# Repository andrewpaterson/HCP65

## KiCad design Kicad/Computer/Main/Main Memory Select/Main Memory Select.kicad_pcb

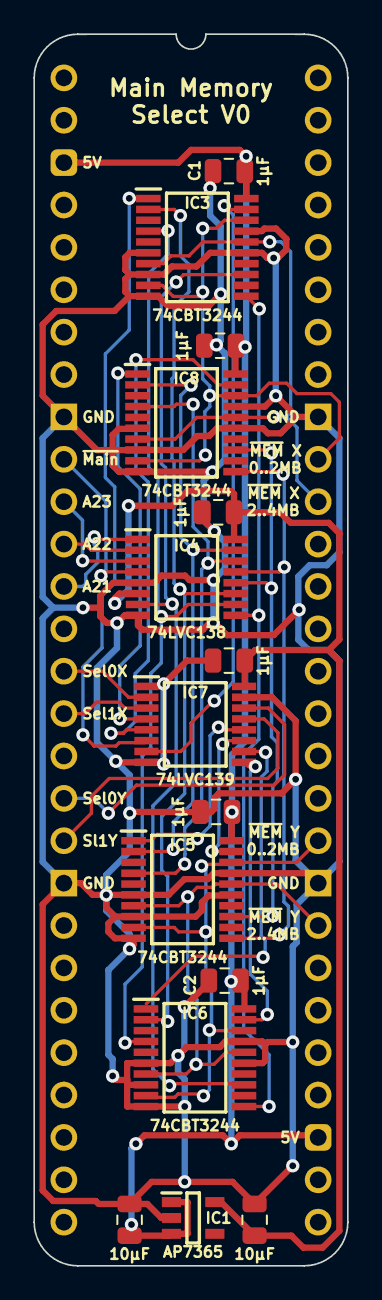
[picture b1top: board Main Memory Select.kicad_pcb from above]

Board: 2 copper layers, 18.8 x 73.8 mm, 16 parts (0 on the bottom side), 31 nets.

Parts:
C1, C2, C3, C5, C9, C12: 1μF; C_0805
C10, C11: 10µF; C_0805
IC1: AP7365-33WG-7; SOT95P285X130-5N
IC3, IC5, IC6, IC8: SN74CBT3244CPWR; SOP65P640X120-20N
IC4: 74LVC138APW-Q100J; SOP65P640X110-16N
IC7: 74LVC139PW,118; SOP65P640X110-16N
J1: Board 2x28 W15.24mm; DIP-56_Board_W15.24mm

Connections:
5V: C1.1, C2.1, C3.1, C9.1, C10.1, IC1.1 (6VIn), IC1.3 (EN), IC3.20 (5V), IC5.20 (5V), IC6.20 (5V), IC8.20 (5V), J1.3, J1.31
/3.3V: C5.1, C11.1, C12.1, IC1.5 (3.3VOut), IC4.6 (E3), IC4.16 (3V), IC7.16 (3V)
/Memory 0..2MB ~CS: IC4.15 (~Y0), IC5.2 (1A1), IC8.2 (1A1)
/Memory 0..4MB_{ Device}X: IC7.4 (~1Y0), IC8.1 (1~OE)
/Memory 0..4MB_{ Device}Y: IC5.1 (1~OE), IC7.12 (~2Y0)
/Memory 2..4MB ~CS: IC4.14 (~Y1), IC5.4 (1A2), IC8.4 (1A2)
/Memory 4..6MB ~CS: IC4.13 (~Y2), IC5.11 (2A1), IC8.11 (2A1)
/Memory 4..8MB_{ Device}X: IC7.5 (~1Y1), IC8.19 (2~OE)
/Memory 4..8MB_{ Device}Y: IC5.19 (2~OE), IC7.11 (~2Y1)
/Memory 6..8MB ~CS: IC4.12 (~Y3), IC5.13 (2A2), IC8.13 (2A2)
/Memory 8..10MB ~CS: IC3.2 (1A1), IC4.11 (~Y4), IC6.2 (1A1)
/Memory 8..12MB_{ Device}X: IC3.1 (1~OE), IC7.6 (~1Y2)
/Memory 8..12MB_{ Device}Y: IC6.1 (1~OE), IC7.10 (~2Y2)
/Memory 10..12MB ~CS: IC3.4 (1A2), IC4.10 (~Y5), IC6.4 (1A2)
/Memory 12..14MB ~CS: IC3.11 (2A1), IC4.9 (~Y6), IC6.11 (2A1)
/Memory 12..16MB_{ Device}X: IC3.19 (2~OE), IC7.7 (~1Y3)
/Memory 12..16MB_{ Device}Y: IC6.19 (2~OE), IC7.9 (~2Y3)
/Memory 14..16MB ~CS: IC3.13 (2A2), IC4.7 (~Y7), IC6.13 (2A2)
AM21: IC4.1 (A0), J1.13
AM22: IC4.2 (A1), J1.12
AM23: IC4.3 (A2), J1.11
GND: C1.2, C2.2, C3.2, C5.2, C9.2, C10.2, C11.2, C12.2, IC1.2 (GND), IC3.6 (1A3), IC3.8 (1A4), IC3.10 (GND), IC3.15 (2A3), IC3.17 (2A4), IC4.5 (~E2), IC4.8 (GND), IC5.6 (1A3), IC5.8 (1A4), IC5.10 (GND), IC5.15 (2A3), IC5.17 (2A4), IC6.6 (1A3), IC6.8 (1A4), IC6.10 (GND), IC6.15 (2A3), IC6.17 (2A4), IC7.1 (~1E), IC7.8 (GND), IC7.15 (~2E), IC8.6 (1A3), IC8.8 (1A4), IC8.10 (GND), IC8.15 (2A3), IC8.17 (2A4), J1.9, J1.20, J1.37, J1.48
Select 0_{ Device}X: IC7.2 (1A0), J1.15
Select 0_{ Device}Y: IC7.14 (2A0), J1.18
Select 1_{ Device}X: IC7.3 (1A1), J1.16
Select 1_{ Device}Y: IC7.13 (2A1), J1.19
~Main_{M}: IC4.4 (~E1), J1.10
~Memory _{0..2MB}_{ Device}X: IC3.9 (2B1), IC3.18 (1B1), IC8.9 (2B1), IC8.18 (1B1), J1.47
~Memory _{0..2MB}_{ Device}Y: IC5.9 (2B1), IC5.18 (1B1), IC6.9 (2B1), IC6.18 (1B1), J1.38
~Memory _{2..4MB}_{ Device}X: IC3.7 (2B2), IC3.16 (1B2), IC8.7 (2B2), IC8.16 (1B2), J1.46
~Memory _{2..4MB}_{ Device}Y: IC5.7 (2B2), IC5.16 (1B2), IC6.7 (2B2), IC6.16 (1B2), J1.36

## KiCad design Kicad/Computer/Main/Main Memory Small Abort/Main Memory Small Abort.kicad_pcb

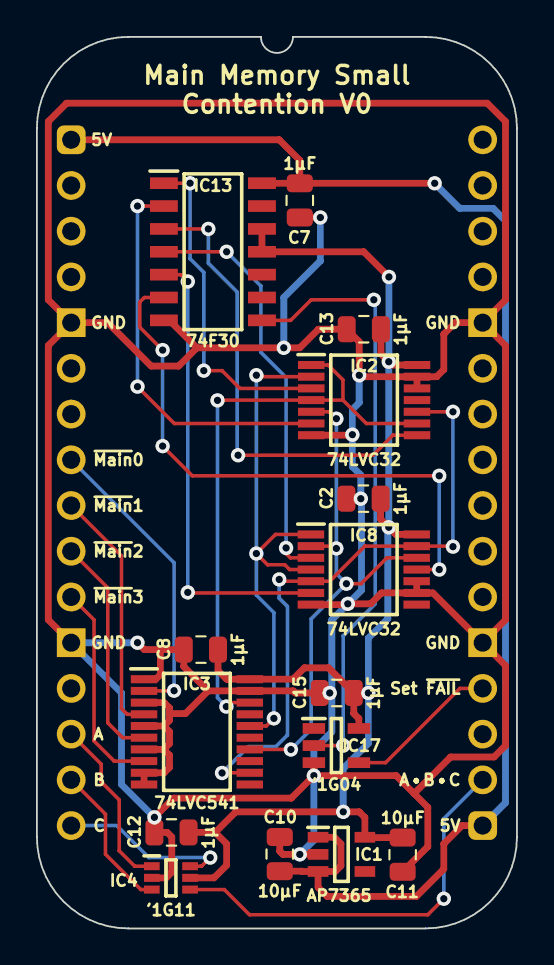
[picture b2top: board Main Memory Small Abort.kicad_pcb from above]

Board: 2 copper layers, 26.7 x 49.5 mm, 16 parts (0 on the bottom side), 23 nets.

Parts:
C2, C7, C8, C12, C13, C15: 1μF; C_0805
C10, C11: 10µF; C_0805
IC1: AP7365-33WG-7; SOT95P285X130-5N
IC2, IC8: 74LVC32APW,118; SOP65P640X110-14N
IC3: 74LVC541APW,118; SOP65P640X110-20N
IC4: 74LVC1G11GW-Q100H; SOP65P210X110-6N
IC13: SN74F30DR; SOIC127P600X175-14N
IC17: 74LVC1G04GV,125; SOT95P275X110-5N
J1: Board 2x16 W22.86mm; DIP-32_Board_W22.86mm

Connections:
5V: C7.1, C10.1, IC1.1 (6VIn), IC1.3 (EN), IC13.14 (5V), J1.1, J1.17
/3.3V: C2.1, C8.1, C11.1, C12.1, C13.1, C15.1, IC1.5 (3.3VOut), IC2.14 (3V), IC3.20 (3V), IC4.5 (3V), IC8.14 (3V), IC13.11 (G), IC13.12 (H), IC17.5 (3V)
/~0+1: IC2.3 (1Y), IC13.1 (A)
/~0+2: IC2.6 (2Y), IC13.2 (B)
/~0+3: IC2.8 (3Y), IC13.3 (C)
/~1+2: IC8.3 (1Y), IC13.4 (D)
/~1+3: IC8.6 (2Y), IC13.5 (E)
/~2+3: IC8.11 (4Y), IC13.6 (F)
/~MainB0: IC2.1 (1A), IC2.4 (2A), IC2.9 (3A), IC3.18 (Y0)
/~MainB1: IC2.2 (1B), IC3.16 (Y2), IC8.1 (1A), IC8.4 (2A)
/~MainB2: IC2.5 (2B), IC3.14 (Y4), IC8.2 (1B), IC8.12 (4A)
/~MainB3: IC2.10 (3B), IC3.12 (Y6), IC8.5 (2B), IC8.13 (4B)
A: IC4.1 (A), J1.14
A•B•C: IC4.4 (Y), J1.18
B: IC4.3 (B), J1.15
C: IC4.6 (C), J1.16
GND: C2.2, C7.2, C8.2, C10.2, C11.2, C12.2, C13.2, C15.2, IC1.2 (GND), IC2.7 (GND), IC2.12 (4A), IC2.13 (4B), IC3.1 (~OE1), IC3.3 (A1), IC3.5 (A3), IC3.7 (A5), IC3.9 (A7), IC3.10 (GND), IC3.19 (~OE2), IC4.2 (GND), IC8.7 (GND), IC8.9 (3A), IC8.10 (3B), IC13.7 (GND), IC17.3 (GND), J1.5, J1.12, J1.21, J1.28
unnamed: IC13.8 (Y), IC17.2 (A)
~Main0: IC3.2 (A0), J1.8
~Main1: IC3.4 (A2), J1.9
~Main2: IC3.6 (A4), J1.10
~Main3: IC3.8 (A6), J1.11
~Set Contention: IC17.4 (Y), J1.20

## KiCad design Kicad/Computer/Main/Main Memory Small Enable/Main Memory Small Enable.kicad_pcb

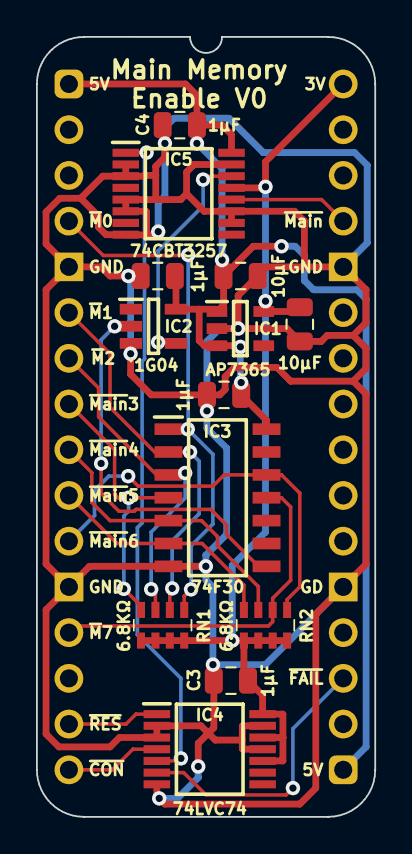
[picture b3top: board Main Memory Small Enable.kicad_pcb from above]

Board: 2 copper layers, 18.8 x 43.3 mm, 14 parts (0 on the bottom side), 18 nets.

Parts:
C1, C3, C4, C6: 1μF; C_0805
C10, C11: 10µF; C_0805
IC1: AP7365-33WG-7; SOT95P285X130-5N
IC2: 74LVC1G04GV,125; SOT95P275X110-5N
IC3: SN74F30DR; SOIC127P600X175-14N
IC4: 74LVC74APW,118; SOP65P640X110-14N
IC5: SN74CBT3257CPWR; SOP65P640X120-16N
J2: Board 2x16 W15.24mm; DIP-32_Board_W15.24mm
RN1, RN2: CAY16-682J4LF; CAY16-J4

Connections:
3.3V: C3.1, C11.1, IC1.5 (3.3VOut), IC4.10 (~2SD), IC4.12 (2D), IC4.14 (3V), IC5.13 (4B2), J2.32, RN1.5 (R4), RN1.6 (R3), RN1.7 (R2), RN1.8 (R1), RN2.5 (R4), RN2.6 (R3), RN2.7 (R2), RN2.8 (R1)
5V: C1.1, C4.1, C6.1, C10.1, IC1.1 (6VIn), IC1.3 (EN), IC2.5 (3V), IC3.14 (5V), IC5.16 (5V), J2.1, J2.17
/Contention: IC4.5 (1Q), IC5.1 (S)
/Pre-Main Memory: IC2.2 (A), IC3.8 (Y)
/~Pre-Main Memory: IC2.4 (Y), IC5.14 (4B1)
GND: C1.2, C3.2, C4.2, C6.2, C10.2, C11.2, IC1.2 (GND), IC2.3 (GND), IC3.7 (GND), IC4.2 (1D), IC4.3 (1CP), IC4.7 (GND), IC4.11 (2CP), IC4.13 (~2RD), IC5.2 (1B1), IC5.3 (1B2), IC5.5 (2B1), IC5.6 (2B2), IC5.8 (GND), IC5.10 (3B2), IC5.11 (3B1), IC5.15 (~OE), J2.5, J2.12, J2.21, J2.28
~Contention: IC4.6 (~1Q), J2.19
~Main Memory: IC5.12 (4A), J2.29
~Main0: IC3.1 (A), J2.4, RN1.1 (R1)
~Main1: IC3.2 (B), J2.6, RN1.2 (R2)
~Main2: IC3.3 (C), J2.7, RN1.3 (R3)
~Main3: IC3.4 (D), J2.8, RN1.4 (R4)
~Main4: IC3.5 (E), J2.9, RN2.3 (R3)
~Main5: IC3.6 (F), J2.10, RN2.4 (R4)
~Main6: IC3.12 (H), J2.11, RN2.1 (R1)
~Main7: IC3.11 (G), J2.13, RN2.2 (R2)
~Reset: IC4.1 (~1RD), J2.15
~Set Contention: IC4.4 (~1SD), J2.16

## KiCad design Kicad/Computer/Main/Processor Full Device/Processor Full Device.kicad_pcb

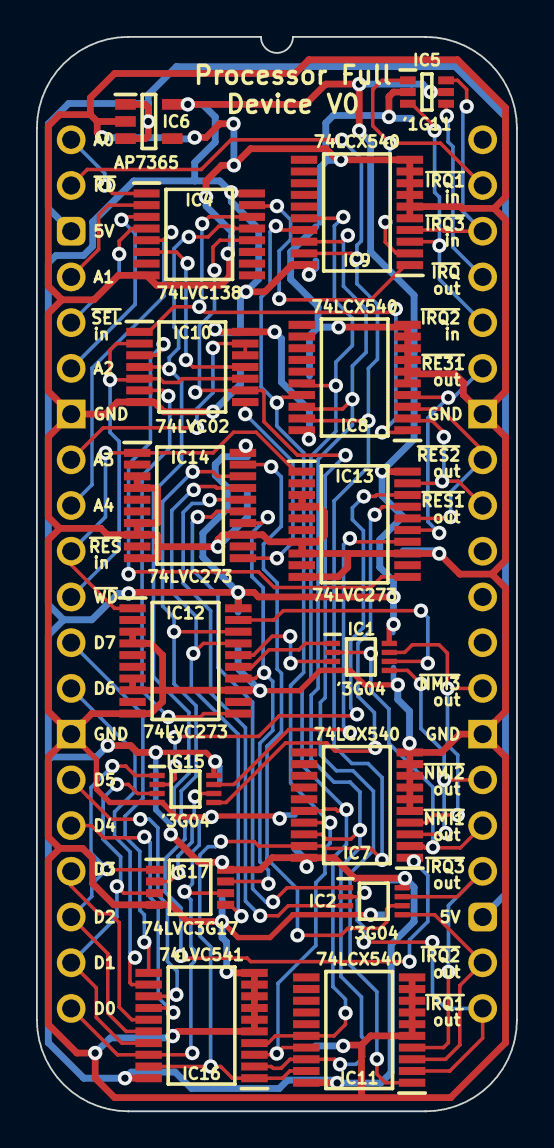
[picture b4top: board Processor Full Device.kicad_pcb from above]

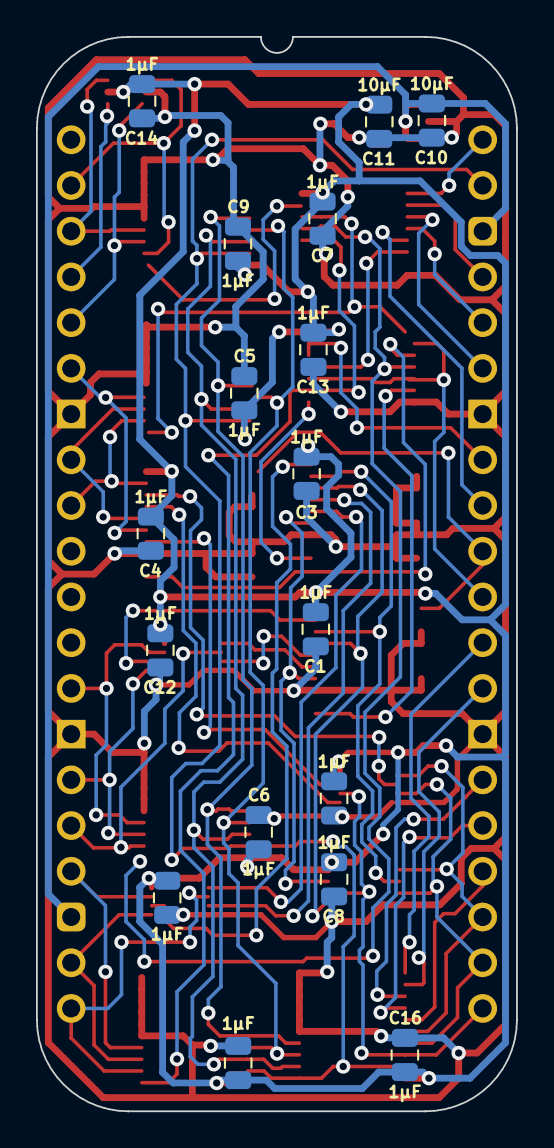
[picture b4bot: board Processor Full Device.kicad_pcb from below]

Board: 2 copper layers, 26.7 x 59.7 mm, 34 parts (17 on the bottom side), 56 nets.

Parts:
C1, C2, C3, C4, C5, C6, C7, C8, C9, C12, C13, C14, C15, C16, C17: 1μF; C_0805
C10, C11: 10µF; C_0805
IC1, IC2, IC15: SN74LVC3G04DCUR; SOP50P310X90-8N
IC4: 74LVC138APW-Q100J; SOP65P640X110-16N
IC5: 74LVC1G11GW-Q100H; SOP65P210X110-6N
IC6: AP7365-33WG-7; SOT95P285X130-5N
IC7, IC8, IC9, IC11: 74LCX540FT; SOP65P640X120-20N
IC10: 74LVC02APW,118; SOP65P640X110-14N
IC12, IC13, IC14: 74LVC273PW,118; SOP65P640X110-20N
IC16: 74LVC541APW,118; SOP65P640X110-20N
IC17: 74LVC3G17DP,125; SOP65P400X110-8N
J1: Board 2x20 W22.86mm; DIP-40_Board_W22.86mm

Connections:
5V: C10.1, IC6.1 (6VIn), IC6.3 (EN), J1.3, J1.23
/3.3V: C1.1, C2.1, C3.1, C4.1, C5.1, C6.1, C7.1, C8.1, C9.1, C11.1, C12.1, C13.1, C14.1, C15.1, C16.1, C17.1, IC1.8 (3V), IC2.8 (3V), IC4.16 (3V), IC5.5 (3V), IC6.5 (3.3VOut), IC7.20 (3V), IC8.20 (3V), IC9.20 (3V), IC10.14 (3V), IC11.20 (3V), IC12.20 (3V), IC13.20 (3V), IC14.20 (3V), IC15.8 (3V), IC16.20 (3V), IC17.8 (3V)
/DI0: IC12.18 (D7), IC14.18 (D7), IC17.2 (3Y)
/DI1: IC12.17 (D6), IC14.17 (D6), IC17.5 (2Y)
/DI2: IC12.14 (D5), IC14.14 (D5), IC17.7 (1Y)
/DO0: IC7.18 (~Y1), IC8.18 (~Y1), IC9.18 (~Y1), IC11.18 (~Y1), IC16.2 (A0)
/DO1: IC7.17 (~Y2), IC8.17 (~Y2), IC9.17 (~Y2), IC11.17 (~Y2), IC16.3 (A1)
/DO2: IC7.16 (~Y3), IC8.16 (~Y3), IC9.16 (~Y3), IC11.16 (~Y3), IC16.4 (A2)
/MPU1 IRQ_{out}: IC2.6 (3A), IC14.19 (Q7)
/MPU1 NMI_{out}: IC1.6 (3A), IC12.19 (Q7)
/MPU2 IRQ_{out}: IC2.3 (2A), IC14.16 (Q6)
/MPU2 NMI_{out}: IC1.3 (2A), IC12.16 (Q6)
/MPU3 IRQ_{out}: IC2.1 (1A), IC14.15 (Q5)
/MPU3 NMI_{out}: IC1.1 (1A), IC12.15 (Q5)
/Y1•WD: IC10.3 (1Y), IC13.11 (CP)
/Y2•WD: IC10.6 (2Y), IC12.11 (CP)
/Y3•WD: IC10.8 (3Y), IC14.11 (CP)
/~A3: IC4.6 (E3), IC10.11 (4Y)
/~D0: IC13.18 (D7), IC15.2 (3Y)
/~D1: IC13.17 (D6), IC15.5 (2Y)
/~D2: IC13.14 (D5), IC15.7 (1Y)
/~Y0: IC4.15 (~Y0), IC9.1 (~OE1)
/~Y1: IC4.14 (~Y1), IC8.1 (~OE1), IC10.1 (1A)
/~Y2: IC4.13 (~Y2), IC7.1 (~OE1), IC10.4 (2A)
/~Y3: IC4.12 (~Y3), IC10.9 (3A), IC11.1 (~OE1)
A0: IC4.1 (A0), J1.1
A1: IC4.2 (A1), J1.4
A2: IC4.3 (A2), J1.6
A3: IC10.12 (4A), IC10.13 (4B), J1.8
A4: IC4.5 (~E2), J1.9
D0: IC15.6 (3A), IC16.18 (Y0), IC17.6 (3A), J1.20
D1: IC15.3 (2A), IC16.17 (Y1), IC17.3 (2A), J1.19
D2: IC15.1 (1A), IC16.16 (Y2), IC17.1 (1A), J1.18
D3: IC16.15 (Y3), J1.17
D4: IC16.14 (Y4), J1.16
D5: IC16.13 (Y5), J1.15
D6: IC16.12 (Y6), J1.13
D7: IC16.11 (Y7), J1.12
GND: C1.2, C2.2, C3.2, C4.2, C5.2, C6.2, C7.2, C8.2, C9.2, C10.2, C11.2, C12.2, C13.2, C14.2, C15.2, C16.2, C17.2, IC1.4 (GND), IC2.4 (GND), IC4.8 (GND), IC5.2 (GND), IC6.2 (GND), IC7.5 (A4), IC7.6 (A5), IC7.7 (A6), IC7.8 (A7), IC7.9 (A8), IC7.10 (GND), IC8.5 (A4), IC8.6 (A5), IC8.7 (A6), IC8.8 (A7), IC8.9 (A8), IC8.10 (GND), IC9.5 (A4), IC9.6 (A5), IC9.7 (A6), IC9.8 (A7), IC9.9 (A8), IC9.10 (GND), IC10.7 (GND), IC11.5 (A4), IC11.6 (A5), IC11.7 (A6), IC11.8 (A7), IC11.9 (A8), IC11.10 (GND), IC12.3 (D0), IC12.4 (D1), IC12.7 (D2), IC12.8 (D3), IC12.10 (GND), IC12.13 (D4), IC13.3 (D0), IC13.4 (D1), IC13.7 (D2), IC13.8 (D3), IC13.10 (GND), IC13.13 (D4), IC14.3 (D0), IC14.4 (D1), IC14.7 (D2), IC14.8 (D3), IC14.10 (GND), IC14.13 (D4), IC15.4 (GND), IC16.5 (A3), IC16.6 (A4), IC16.7 (A5), IC16.8 (A6), IC16.9 (A7), IC16.10 (GND), IC17.4 (GND), J1.7, J1.14, J1.27, J1.34
~Device Interrupt: IC5.4 (Y), J1.37
~Device Reset: IC12.1 (~MR), IC13.1 (~MR), IC14.1 (~MR), J1.10
~Device Select: IC4.4 (~E1), J1.5
~MPU1 IRQ_{in}: IC5.1 (A), IC9.2 (A1), J1.39
~MPU1 IRQ_{out}: IC2.2 (3Y), IC11.2 (A1), J1.21
~MPU1 NMI_{out}: IC1.2 (3Y), IC7.2 (A1), J1.25
~MPU1 Reset_{out}: IC8.2 (A1), IC13.19 (Q7), J1.32
~MPU2 IRQ_{in}: IC5.3 (B), IC9.3 (A2), J1.36
~MPU2 IRQ_{out}: IC2.5 (2Y), IC11.3 (A2), J1.22
~MPU2 NMI_{out}: IC1.5 (2Y), IC7.3 (A2), J1.26
~MPU2 Reset_{out}: IC8.3 (A2), IC13.16 (Q6), J1.33
~MPU3 IRQ_{in}: IC5.6 (C), IC9.4 (A3), J1.38
~MPU3 IRQ_{out}: IC2.7 (1Y), IC11.4 (A3), J1.24
~MPU3 NMI_{out}: IC1.7 (1Y), IC7.4 (A3), J1.28
~MPU3 Reset_{out}: IC8.4 (A3), IC13.15 (Q5), J1.35
~RD: IC7.19 (~OE2), IC8.19 (~OE2), IC9.19 (~OE2), IC11.19 (~OE2), IC16.1 (~OE1), IC16.19 (~OE2), J1.2
~WD: IC10.2 (1B), IC10.5 (2B), IC10.10 (3B), J1.11

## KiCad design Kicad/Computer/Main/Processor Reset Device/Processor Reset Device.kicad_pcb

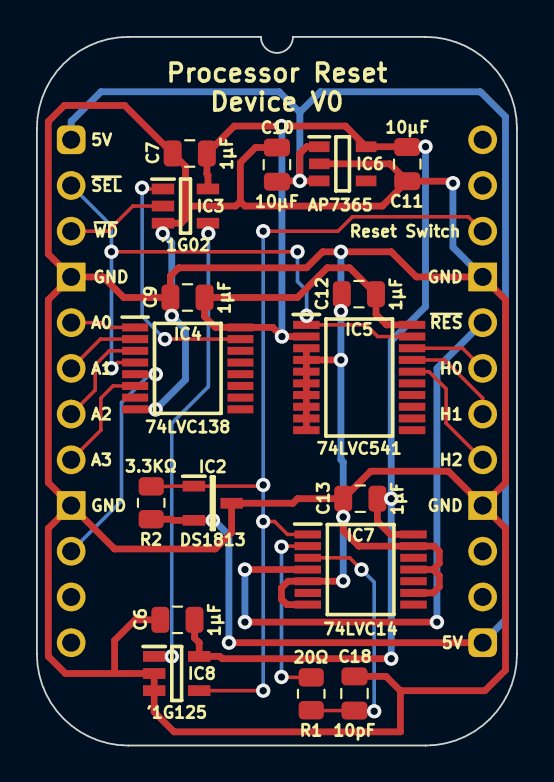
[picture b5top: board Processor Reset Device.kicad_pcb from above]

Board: 2 copper layers, 26.7 x 39.4 mm, 19 parts (1 on the bottom side), 19 nets.

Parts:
C6, C7, C9, C12, C13: 1μF; C_0805
C10, C11: 10µF; C_0805
C18: 10pF; C_0805
IC2: DS1813R-10+T&R; SOT95P237X112-3N
IC3: 74LVC1G02GV,125; SOT95P275X110-5N
IC4: 74LVC138APW-Q100J; SOP65P640X110-16N
IC5: 74LVC541APW,118; SOP65P640X110-20N
IC6: AP7365-33WG-7; SOT95P285X130-5N
IC7: 74LVC14APW,118; SOP65P640X110-14N
IC8: 74LVC1G125GV-Q100; SOT95P275X110-5N
J1: Board 2x12 W22.86mm; DIP-24_Board_W22.86mm
J4: Pin_Header_01x12; PinHeader_1x12_P2.54mm_Vertical
R1: 20Ω; R_0805
R2: 3.3KΩ; R_0805

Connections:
5V: C10.1, IC2.2 (5V), IC6.1 (6VIn), IC6.3 (EN), J1.1, J1.13, R2.2
/3.3V: C6.1, C7.1, C9.1, C11.1, C12.1, C13.1, IC3.5 (3V), IC4.16 (3V), IC5.2 (A0), IC5.20 (3V), IC6.5 (3.3VOut), IC7.14 (3V), IC8.5 (3V)
/Reset_{1}: IC7.2 (1Y), R1.1
/Reset_{2}: C18.1, IC7.3 (2A), R1.2
/~WD•~Y0: IC3.4 (Y), IC8.1 (~OE)
/~Y0: IC3.1 (B), IC4.15 (~Y0)
A0: IC4.1 (A0), J1.5
A1: IC4.2 (A1), J1.6
A2: IC4.3 (A2), J1.7
A3: IC4.6 (E3), J1.8
A4: IC4.5 (~E2), J1.10
GND: C6.2, C7.2, C9.2, C10.2, C11.2, C12.2, C13.2, C18.2, IC2.3 (GND), IC3.3 (GND), IC4.8 (GND), IC5.3 (A1), IC5.4 (A2), IC5.5 (A3), IC5.6 (A4), IC5.7 (A5), IC5.8 (A6), IC5.9 (A7), IC5.10 (GND), IC6.2 (GND), IC7.5 (3A), IC7.7 (GND), IC7.9 (4A), IC7.11 (5A), IC7.13 (6A), IC8.2 (A), IC8.3 (GND), J1.4, J1.9, J1.16, J1.21
H0: IC5.18 (Y0), J1.19
H1: IC5.17 (Y1), J1.18
H2: IC5.16 (Y2), J1.17
~Device Select: IC4.4 (~E1), IC5.1 (~OE1), IC5.19 (~OE2), J1.2
~Reset Switch: IC2.1 (~RST), IC7.1 (1A), IC8.4 (Y), J1.22, R2.1
~Reset: IC7.4 (2Y), J1.20
~WD: IC3.2 (A), J1.3

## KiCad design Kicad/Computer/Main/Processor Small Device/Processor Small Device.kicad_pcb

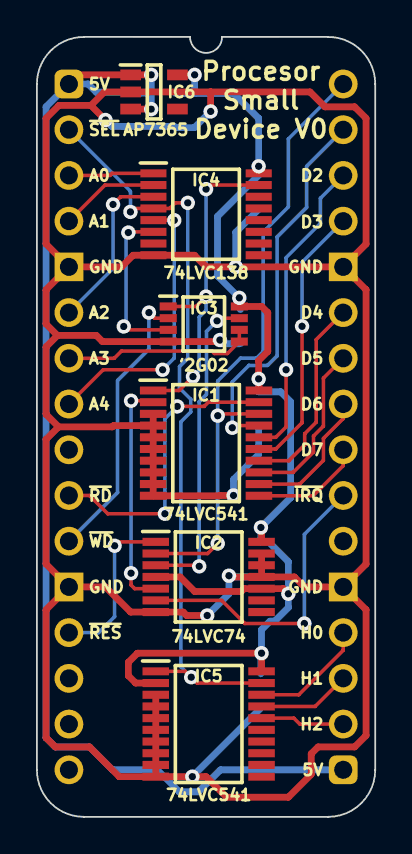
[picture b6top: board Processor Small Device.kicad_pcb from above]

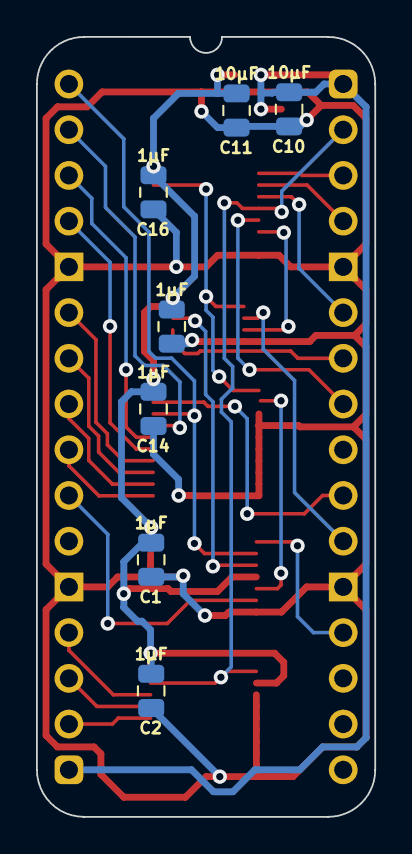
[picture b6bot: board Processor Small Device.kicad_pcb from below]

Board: 2 copper layers, 18.8 x 43.3 mm, 14 parts (7 on the bottom side), 28 nets.

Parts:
C1, C2, C14, C15, C16: 1μF; C_0805
C10, C11: 10µF; C_0805
IC1, IC5: 74LVC541APW,118; SOP65P640X110-20N
IC2: 74LVC74APW,118; SOP65P640X110-14N
IC3: 74LVC2G02DP,125; SOP65P400X110-8N
IC4: 74LVC138APW-Q100J; SOP65P640X110-16N
IC6: AP7365-33WG-7; SOT95P285X130-5N
J1: Board 2x16 W15.24mm; DIP-32_Board_W15.24mm

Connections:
5V: C10.1, IC6.1 (6VIn), IC6.3 (EN), J1.1, J1.17
/3.3V: C1.1, C2.1, C11.1, C14.1, C15.1, C16.1, IC1.20 (3V), IC2.4 (~1SD), IC2.10 (~2SD), IC2.14 (3V), IC3.8 (3V), IC4.16 (3V), IC5.2 (A0), IC5.20 (3V), IC6.5 (3.3VOut)
/MPU0 IRQ_{out}: IC1.2 (A0), IC2.5 (1Q)
/Y0•WD: IC2.3 (1CP), IC3.7 (1Y)
/~A3: IC3.3 (2Y), IC4.6 (E3)
/~Y0: IC1.1 (~OE1), IC3.1 (1A), IC4.15 (~Y0)
A0: IC4.1 (A0), J1.3
A1: IC4.2 (A1), J1.4
A2: IC4.3 (A2), J1.6
A3: IC3.5 (2A), IC3.6 (2B), J1.7
A4: IC4.5 (~E2), J1.8
D0: IC1.18 (Y0), IC2.2 (1D), J1.32
D1: IC1.17 (Y1), J1.31
D2: IC1.16 (Y2), J1.30
D3: IC1.15 (Y3), J1.29
D4: IC1.14 (Y4), J1.27
D5: IC1.13 (Y5), J1.26
D6: IC1.12 (Y6), J1.25
D7: IC1.11 (Y7), J1.24
GND: C1.2, C2.2, C10.2, C11.2, C14.2, C15.2, C16.2, IC1.3 (A1), IC1.4 (A2), IC1.5 (A3), IC1.6 (A4), IC1.7 (A5), IC1.8 (A6), IC1.9 (A7), IC1.10 (GND), IC2.7 (GND), IC2.11 (2CP), IC2.12 (2D), IC2.13 (~2RD), IC3.4 (GND), IC4.8 (GND), IC5.3 (A1), IC5.4 (A2), IC5.5 (A3), IC5.6 (A4), IC5.7 (A5), IC5.8 (A6), IC5.9 (A7), IC5.10 (GND), IC6.2 (GND), J1.5, J1.12, J1.21, J1.28
H0: IC5.18 (Y0), J1.20
H1: IC5.17 (Y1), J1.19
H2: IC5.16 (Y2), J1.18
~Device Reset: IC2.1 (~1RD), J1.13
~Device Select: IC4.4 (~E1), IC5.1 (~OE1), IC5.19 (~OE2), J1.2
~MPU0 IRQ_{out}: IC2.6 (~1Q), J1.23
~RD: IC1.19 (~OE2), J1.10
~WD: IC3.2 (1B), J1.11

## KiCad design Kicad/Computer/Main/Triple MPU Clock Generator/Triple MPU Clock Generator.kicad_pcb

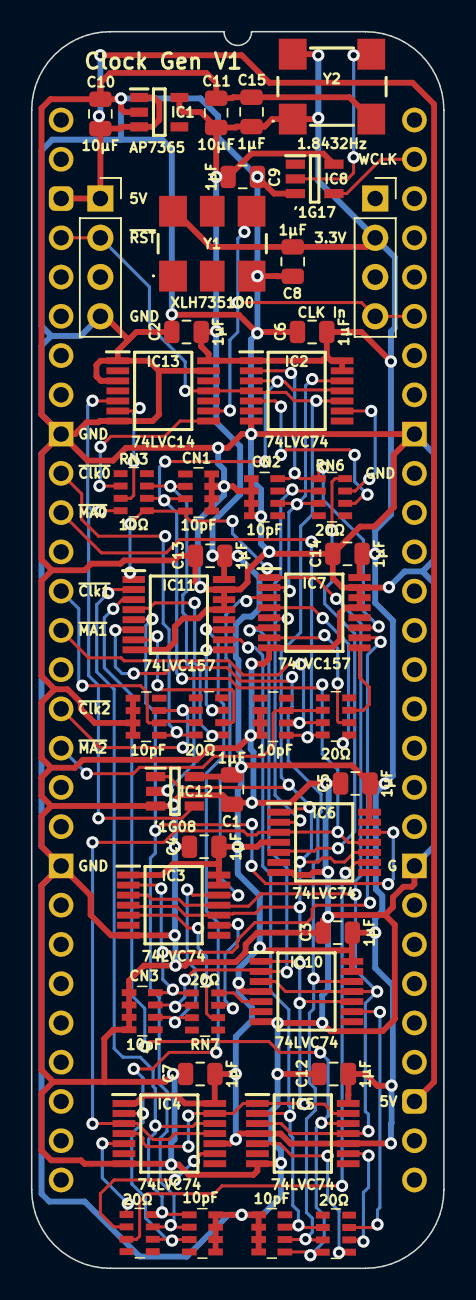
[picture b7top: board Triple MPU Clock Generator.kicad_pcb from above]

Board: 2 copper layers, 26.7 x 80.0 mm, 46 parts (0 on the bottom side), 49 nets.

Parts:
C1, C2, C3, C4, C5, C6, C7, C8, C9, C12, C13, C14, C15: 1μF; C_0805
C10, C11: 10µF; C_0805
CN1, CN2, CN3, CN4, CN5, CN7, CN8: CA0612KRX7R9BB100
IC1: AP7365-33WG-7; SOT95P285X130-5N
IC2, IC3, IC4, IC5, IC6, IC10: 74LVC74APW,118; SOP65P640X110-14N
IC7, IC11: 74LVC157APW,118; SOP65P640X110-16N
IC8: 74LVC1G17GV,125; SOT95P275X110-5N
IC12: 74LVC1G08GV,125; SOT95P275X110-5N
IC13: 74LVC14APW,118; SOP65P640X110-14N
J2: Board 2x28 W22.86mm; DIP-56_Board_W22.86mm
J4, J5: Conn_01x04_Socket; PinSocket_1x04_P2.54mm_Vertical
RN2, RN4, RN6, RN7, RN8, RN9: CAY16-200J4LF; CAY16-F4
RN3: CAY16-100J4LF; CAY16-F4
Y1: XLH735100.000000I; XLH735100000000I
Y2: LFSPXO020733

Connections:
5V: C10.1, IC1.1 (6VIn), IC1.3 (EN), J2.3, J2.31, J4.1
/3.3V: C1.1, C2.1, C3.1, C4.1, C5.1, C6.1, C7.1, C8.1, C9.1, C11.1, C12.1, C13.1, C14.1, C15.1, IC1.5 (3.3VOut), IC2.1 (~1RD), IC2.13 (~2RD), IC2.14 (3V), IC3.1 (~1RD), IC3.13 (~2RD), IC3.14 (3V), IC4.1 (~1RD), IC4.10 (~2SD), IC4.14 (3V), IC5.4 (~1SD), IC5.10 (~2SD), IC5.14 (3V), IC6.4 (~1SD), IC6.13 (~2RD), IC6.14 (3V), IC7.16 (3V), IC8.5 (3V), IC10.4 (~1SD), IC10.13 (~2RD), IC10.14 (3V), IC11.16 (3V), IC12.5 (3V), IC13.14 (3V), J5.2, Y1.6 (3V), Y2.1 (EN), Y2.4 (3V)
/!(R•CLK): IC13.6 (3Y), RN3.3 (R3)
/!(R•CLK)_{s}: CN1.3, IC2.3 (1CP), IC2.11 (2CP), IC4.3 (1CP), IC4.11 (2CP), IC6.3 (1CP), IC6.11 (2CP), RN3.6 (R3)
/CK_{0s}: CN4.1, IC4.12 (2D), IC11.2 (1I0), RN8.8 (R1)
/CK_{0}: IC4.5 (1Q), RN8.1 (R1)
/CK_{1s}: CN5.1, IC5.12 (2D), IC11.3 (1I1), RN9.8 (R1)
/CK_{1}: IC5.5 (1Q), RN9.1 (R1)
/CK_{2s}: CN4.2, IC6.12 (2D), IC11.5 (2I0), RN8.7 (R2)
/CK_{2}: IC4.9 (2Q), RN8.2 (R2)
/CK_{3s}: CN5.2, IC10.12 (2D), IC11.6 (2I1), RN9.7 (R2)
/CK_{3}: IC5.9 (2Q), RN9.2 (R2)
/CK_{4s}: CN4.3, IC4.2 (1D), IC11.11 (3I0), RN8.6 (R3)
/CK_{4}: IC6.9 (2Q), RN8.3 (R3)
/CK_{5s}: CN5.3, IC5.2 (1D), IC11.10 (3I1), RN9.6 (R3)
/CK_{5}: IC10.9 (2Q), RN9.3 (R3)
/MA_{0s}: CN2.2, IC2.12 (2D), IC7.2 (1I0), RN6.7 (R2)
/MA_{0}: IC2.5 (1Q), RN6.2 (R2)
/MA_{1s}: CN3.2, IC3.12 (2D), IC7.3 (1I1), RN7.7 (R2)
/MA_{1}: IC3.5 (1Q), RN7.2 (R2)
/MA_{2s}: CN2.3, IC6.2 (1D), IC7.5 (2I0), RN6.6 (R3)
/MA_{2}: IC2.9 (2Q), RN6.3 (R3)
/MA_{3s}: CN3.3, IC7.6 (2I1), IC10.2 (1D), RN7.6 (R3)
/MA_{3}: IC3.9 (2Q), RN7.3 (R3)
/MA_{4s}: CN2.4, IC2.2 (1D), IC7.11 (3I0), RN6.5 (R4)
/MA_{4}: IC6.5 (1Q), RN6.4 (R4)
/MA_{5s}: CN3.4, IC3.2 (1D), IC7.10 (3I1), RN7.5 (R4)
/MA_{5}: IC10.5 (1Q), RN7.4 (R4)
/R•CLK: IC12.4 (Y), IC13.5 (3A), RN3.4 (R4)
/R•CLK_{s}: CN1.4, IC3.3 (1CP), IC3.11 (2CP), IC5.3 (1CP), IC5.11 (2CP), IC7.1 (S), IC10.3 (1CP), IC10.11 (2CP), IC11.1 (S), RN3.5 (R4)
/~CLK: IC13.8 (4Y), RN3.2 (R2)
/~CLK_{s}: CN1.2, IC12.2 (A), RN3.7 (R2)
CLK: IC13.9 (4A), J2.51, J5.4, Y1.4 (OUT)
GND: C1.2, C2.2, C3.2, C4.2, C5.2, C6.2, C7.2, C8.2, C9.2, C10.2, C11.2, C12.2, C13.2, C14.2, C15.2, CN1.5, CN1.6, CN1.7, CN1.8, CN2.5, CN2.6, CN2.7, CN2.8, CN3.5, CN3.6, CN3.7, CN3.8, CN4.5, CN4.6, CN4.7, CN4.8, CN5.5, CN5.6, CN5.7, CN5.8, CN7.6, CN7.7, CN7.8, CN8.5, CN8.6, CN8.7, CN8.8, IC1.2 (GND), IC2.7 (GND), IC3.7 (GND), IC4.7 (GND), IC5.7 (GND), IC6.7 (GND), IC7.8 (GND), IC7.13 (4I1), IC7.14 (4I0), IC7.15 (~E), IC8.3 (GND), IC10.7 (GND), IC11.8 (GND), IC11.13 (4I1), IC11.14 (4I0), IC11.15 (~E), IC12.3 (GND), IC13.1 (1A), IC13.3 (2A), IC13.7 (GND), IC13.13 (6A), J2.9, J2.20, J2.37, J2.48, J4.4, Y1.3 (GND), Y2.2 (GND)
unnamed: IC7.4 (1Y), RN2.5 (R4)
unnamed: IC7.7 (2Y), RN2.6 (R3)
unnamed: IC7.9 (3Y), RN2.7 (R2)
unnamed: IC8.2 (A), Y2.3 (OUT)
unnamed: IC11.4 (1Y), RN4.5 (R4)
unnamed: IC11.7 (2Y), RN4.6 (R3)
unnamed: IC11.9 (3Y), RN4.7 (R2)
WATCH CLK: IC8.4 (Y), J2.55
~MPU Clock0: CN8.1, J2.10, RN4.4 (R4)
~MPU Clock1: CN8.2, J2.13, RN4.3 (R3)
~MPU Clock2: CN8.3, J2.16, RN4.2 (R2)
~Main Access0: CN7.1, J2.11, RN2.4 (R4)
~Main Access1: CN7.2, J2.14, RN2.3 (R3)
~Main Access2: CN7.3, J2.17, RN2.2 (R2)
~Reset: IC2.4 (~1SD), IC2.10 (~2SD), IC3.4 (~1SD), IC3.10 (~2SD), IC4.4 (~1SD), IC4.13 (~2RD), IC5.1 (~1RD), IC5.13 (~2RD), IC6.1 (~1RD), IC6.10 (~2SD), IC10.1 (~1RD), IC10.10 (~2SD), IC12.1 (B), IC13.11 (5A), J2.4, J4.2

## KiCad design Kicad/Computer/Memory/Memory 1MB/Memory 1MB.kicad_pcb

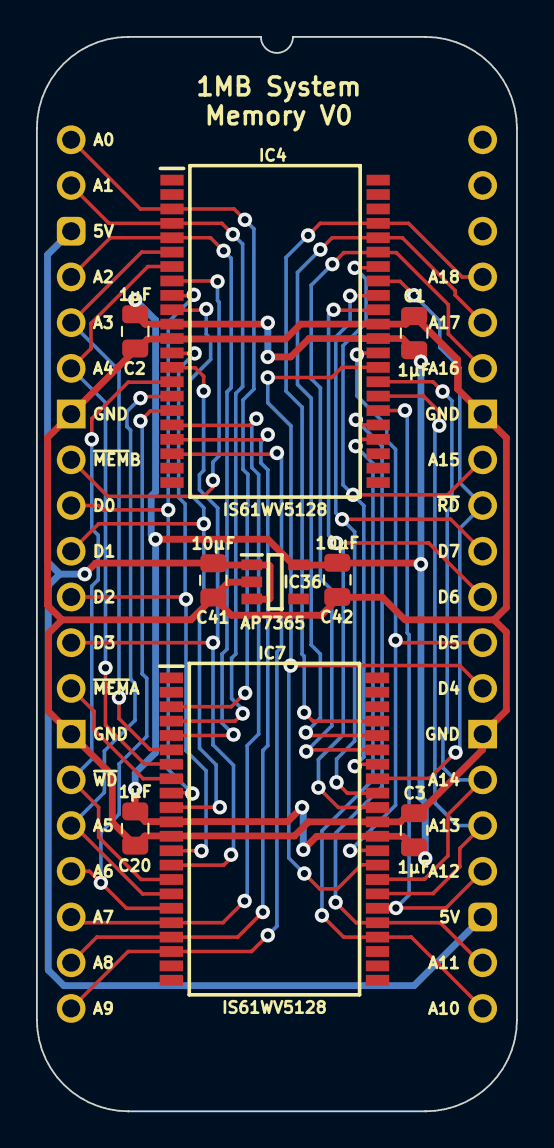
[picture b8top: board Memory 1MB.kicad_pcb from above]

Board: 2 copper layers, 26.7 x 59.7 mm, 10 parts (0 on the bottom side), 34 nets.

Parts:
C1, C2, C3, C20: 1μF; C_0805
C41, C42: 10μF; C_0805
IC4, IC7: IS61WV5128FBLL-10TLI; SOP80P1176X120-44N
IC36: AP7365-33WG-7; SOT95P285X130-5N
J3: Board 2x20 W22.86mm; DIP-40_Board_W22.86mm

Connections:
5V: C41.1, IC36.1 (6VIn), IC36.3 (EN), J3.3, J3.23
/3.3V: C1.1, C2.1, C3.1, C20.1, C42.1, IC4.11 (3V), IC4.33 (3V), IC7.11 (3V), IC7.33 (3V), IC36.5 (3.3VOut)
A0: IC4.3 (A0), IC7.3 (A0), J3.1
A1: IC4.4 (A1), IC7.4 (A1), J3.2
A2: IC4.5 (A2), IC7.5 (A2), J3.4
A3: IC4.6 (A3), IC7.6 (A3), J3.5
A4: IC4.7 (A4), IC7.7 (A4), J3.6
A5: IC4.16 (A5), IC7.16 (A5), J3.16
A6: IC4.17 (A6), IC7.17 (A6), J3.17
A7: IC4.18 (A7), IC7.18 (A7), J3.18
A8: IC4.19 (A8), IC7.19 (A8), J3.19
A9: IC4.20 (A9), IC7.20 (A9), J3.20
A10: IC4.26 (A10), IC7.26 (A10), J3.21
A11: IC4.27 (A11), IC7.27 (A11), J3.22
A12: IC4.28 (A12), IC7.28 (A12), J3.24
A13: IC4.29 (A13), IC7.29 (A13), J3.25
A14: IC4.30 (A14), IC7.30 (A14), J3.26
A15: IC4.38 (A15), IC7.38 (A15), J3.33
A16: IC4.39 (A16), IC7.39 (A16), J3.35
A17: IC4.40 (A17), IC7.40 (A17), J3.36
A18: IC4.41 (A18), IC7.41 (A18), J3.37
D0: IC4.9 (D0), IC7.9 (D0), J3.9
D1: IC4.10 (D1), IC7.10 (D1), J3.10
D2: IC4.13 (D2), IC7.13 (D2), J3.11
D3: IC4.14 (D3), IC7.14 (D3), J3.12
D4: IC4.31 (D4), IC7.31 (D4), J3.28
D5: IC4.32 (D5), IC7.32 (D5), J3.29
D6: IC4.35 (D6), IC7.35 (D6), J3.30
D7: IC4.36 (D7), IC7.36 (D7), J3.31
GND: C1.2, C2.2, C3.2, C20.2, C41.2, C42.2, IC4.12 (GND), IC4.34 (GND), IC7.12 (GND), IC7.34 (GND), IC36.2 (GND), J3.7, J3.14, J3.27, J3.34
~Memory A: IC7.8 (~CE), J3.13
~Memory B: IC4.8 (~CE), J3.8
~RD: IC4.37 (~OE), IC7.37 (~OE), J3.32
~WD: IC4.15 (~WE), IC7.15 (~WE), J3.15
